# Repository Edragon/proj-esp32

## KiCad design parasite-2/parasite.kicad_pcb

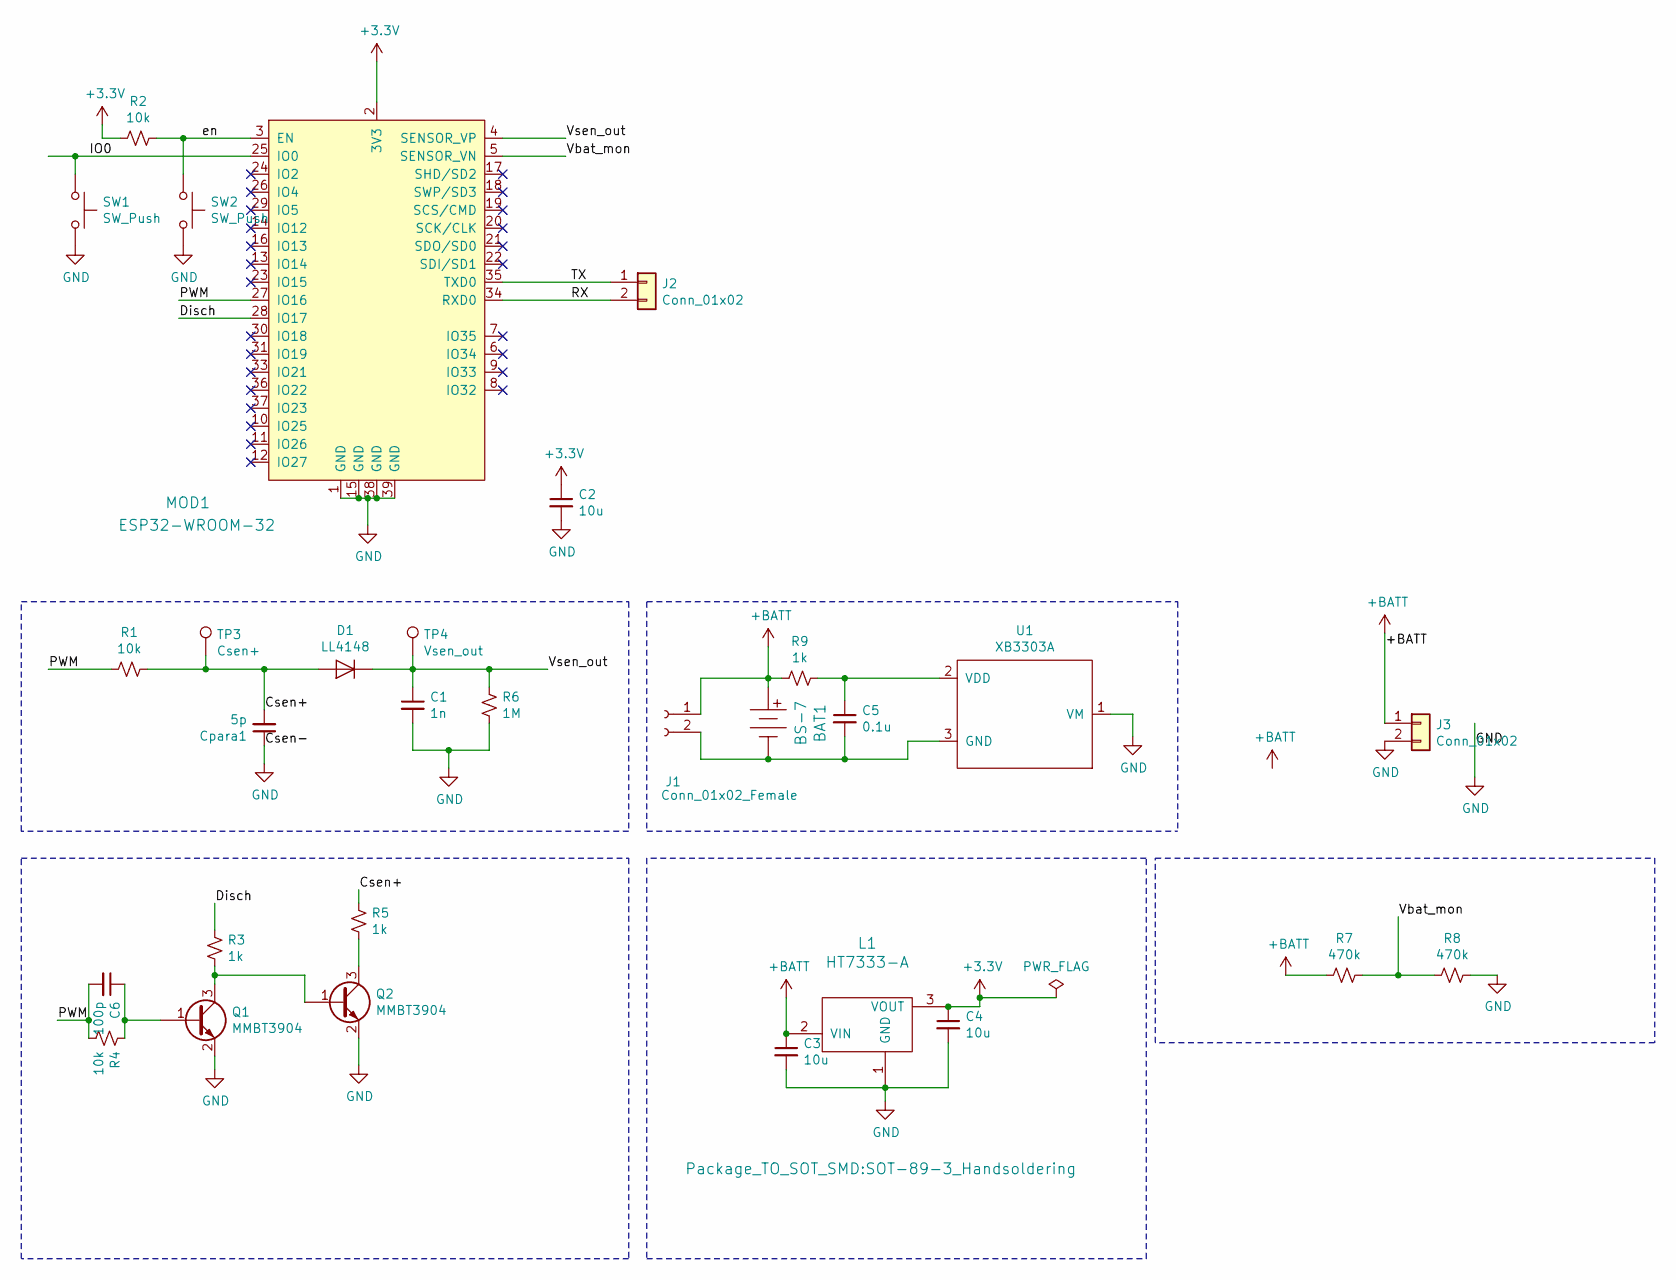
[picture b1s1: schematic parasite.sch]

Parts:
BAT1: BS-7; BatteryHolder_Keystone_3008_1x2450; MPN BS-7; Digi-Key_PN BS-7-ND
C1: 1n; C_0805_2012Metric
C2, C3, C4: 10u; C_0805_2012Metric
C5: 0.1u; C_0805_2012Metric
C6: 100p; C_0805_2012Metric
Cpara1: 5p; C_0805_2012Metric
D1: LL4148; D_MiniMELF
J1: Conn_01x02_Female; JST_PH_S2B-PH-K_1x02_P2.00mm_Horizontal
J2, J3: Conn_01x02; PinHeader_1x02_P2.54mm_Vertical
L1: HT7333-A; SOT-89-3_Handsoldering
MOD1: ESP32-WROOM-32; ESP32; MPN ESP32-WROOM-32; Digi-Key_PN 1904-1010-1-ND
Q1, Q2: MMBT3904; SOT-23
R1, R2, R4: 10k; R_0805_2012Metric
R3, R5, R9: 1k; R_0805_2012Metric
R6: 1M; R_0805_2012Metric
R7, R8: 470k; R_0805_2012Metric
SW1, SW2: SW_Push; SW_SPST_EVQPE1
TP3: Csen+; TestPoint_Pad_D1.0mm
TP4: Vsen_out; TestPoint_Pad_D1.0mm
U1: XB3303A; SOT-23

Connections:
+3V3: C2.1, C4.1, L1.3 (VOUT), MOD1.2 (3V3), R2.1
+BATT: BAT1.Pos, C3.1, J1.1, J3.1, L1.2 (VIN), R7.1, R9.1
/Csen+: Cpara1.2, D1.2 (A), R1.2, R5.1, TP3.1
/Disch: MOD1.28 (IO17), R3.1
/IO0: MOD1.25 (IO0), SW1.1
/PWM: C6.2, MOD1.27 (IO16), R1.1, R4.2
/RX: J2.2, MOD1.34 (RXD0)
/TX: J2.1, MOD1.35 (TXD0)
/Vbat_mon: MOD1.5 (SENSOR_VN), R7.2, R8.1
/Vsen_out: C1.1, D1.1 (K), MOD1.4 (SENSOR_VP), R6.1, TP4.1
/en: MOD1.3 (EN), R2.2, SW2.1
GND: C1.2, C2.2, C3.2, C4.2, Cpara1.1, J3.2, L1.1 (GND), MOD1.1 (GND), MOD1.15 (GND), MOD1.38 (GND), MOD1.39 (GND), Q1.2 (E), Q2.2 (E), R6.2, R8.2, SW1.2, SW2.2, U1.1 (VM)
unnamed: BAT1.Neg, C5.2, J1.2, U1.3 (GND)
unnamed: C5.1, R9.2, U1.2 (VDD)
unnamed: C6.1, Q1.1 (B), R4.1
unnamed: Q1.3 (C), Q2.1 (B), R3.2
unnamed: Q2.3 (C), R5.2

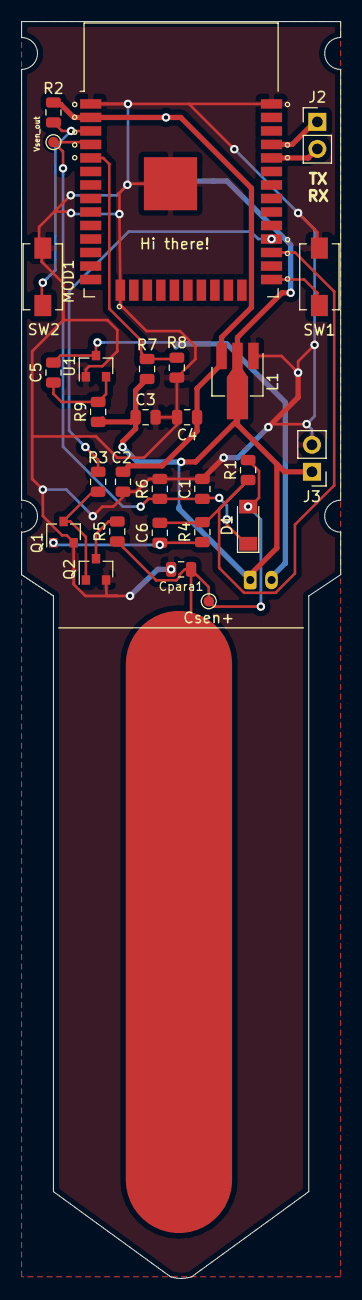
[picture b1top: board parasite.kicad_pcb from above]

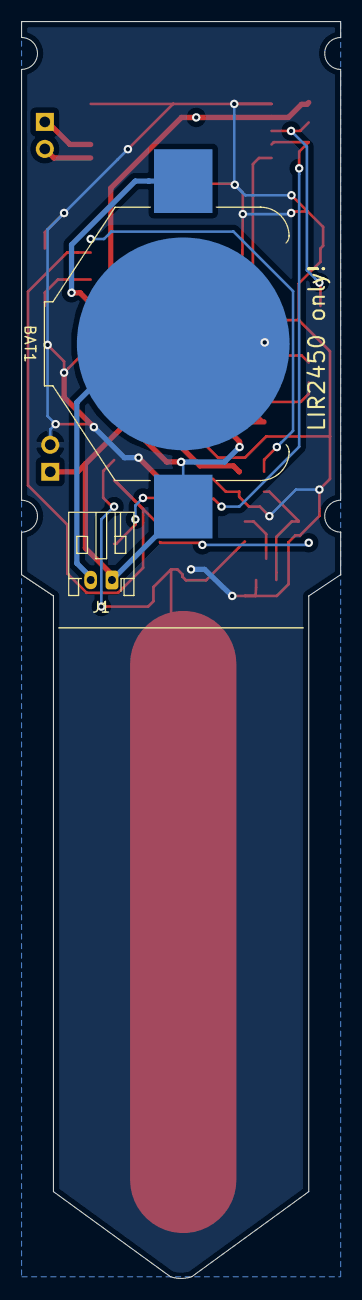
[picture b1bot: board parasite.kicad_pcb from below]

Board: 2 copper layers, 30.0 x 118.2 mm, 30 parts (2 on the bottom side), 17 nets.

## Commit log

2021-04-09 parasite-2
